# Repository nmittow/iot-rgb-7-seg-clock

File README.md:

# iot-rgb-7-seg-clock

RGB leds arranged to simulate the look of a 7 segment display.

Raspberry Pi &amp; ESP32 based controllers.

ESP32 version features: realtime clock, syncs to a network time server,  supports various time display animations.

All PCBs in KiCAD.

Raspberry Pi version features: all ESP32 features plus: 3.5mm audio jack and 5V relay controlled power output (for alarm audio), python library for controlling display &amp; alarm functionality (in-progress).

Motivation: I wanted an alarm that syncs with my various calendars (google, protonmail, etc) capable of 'smart' functionality like adjusting alarm time based on calendar events &amp; traffic conditions, etc., but wanted those calculations to happen locally (i.e. not google now/similar).  Love the look of 7 segment displays but wanted a bit more control of the display.

Construction: PCBs for controllers (ESP32 based &amp; Raspberry Pi cape), 7 segment digits are custom PCBs with APA102 addressable LEDs (3 per segment), daisy-chain-able.  3D Printed shrouds &amp; laser cut acrylic diffuser front, all in a stylish wooden box.  PCBs designed in KiCAD, 3D Modeling in AutoCAD & Fusion360.

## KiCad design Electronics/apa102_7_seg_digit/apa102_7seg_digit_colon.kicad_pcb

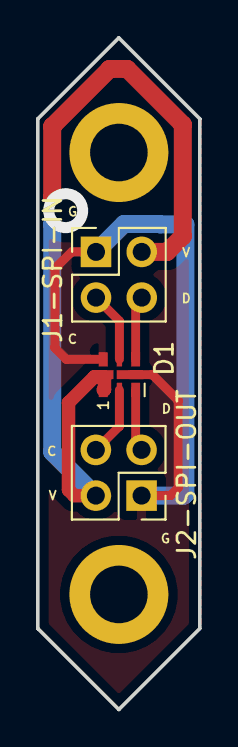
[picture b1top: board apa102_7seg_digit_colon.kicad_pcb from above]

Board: 2 copper layers, 9.0 x 37.3 mm, 3 parts (0 on the bottom side), 6 nets.

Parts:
D1: A_0; LED-APA102-2020
J1-SPI-IN: SPI_IN; PinHeader_2x02_P2.54mm_Vertical
J2-SPI-OUT: SPI_OUT; PinHeader_2x02_P2.54mm_Vertical

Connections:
+5V: D1.1, J1-SPI-IN.2, J2-SPI-OUT.2
GND: D1.6, J1-SPI-IN.1, J2-SPI-OUT.1
unnamed: D1.2, J2-SPI-OUT.4
unnamed: D1.3, J2-SPI-OUT.3
unnamed: D1.4, J1-SPI-IN.4
unnamed: D1.5, J1-SPI-IN.3

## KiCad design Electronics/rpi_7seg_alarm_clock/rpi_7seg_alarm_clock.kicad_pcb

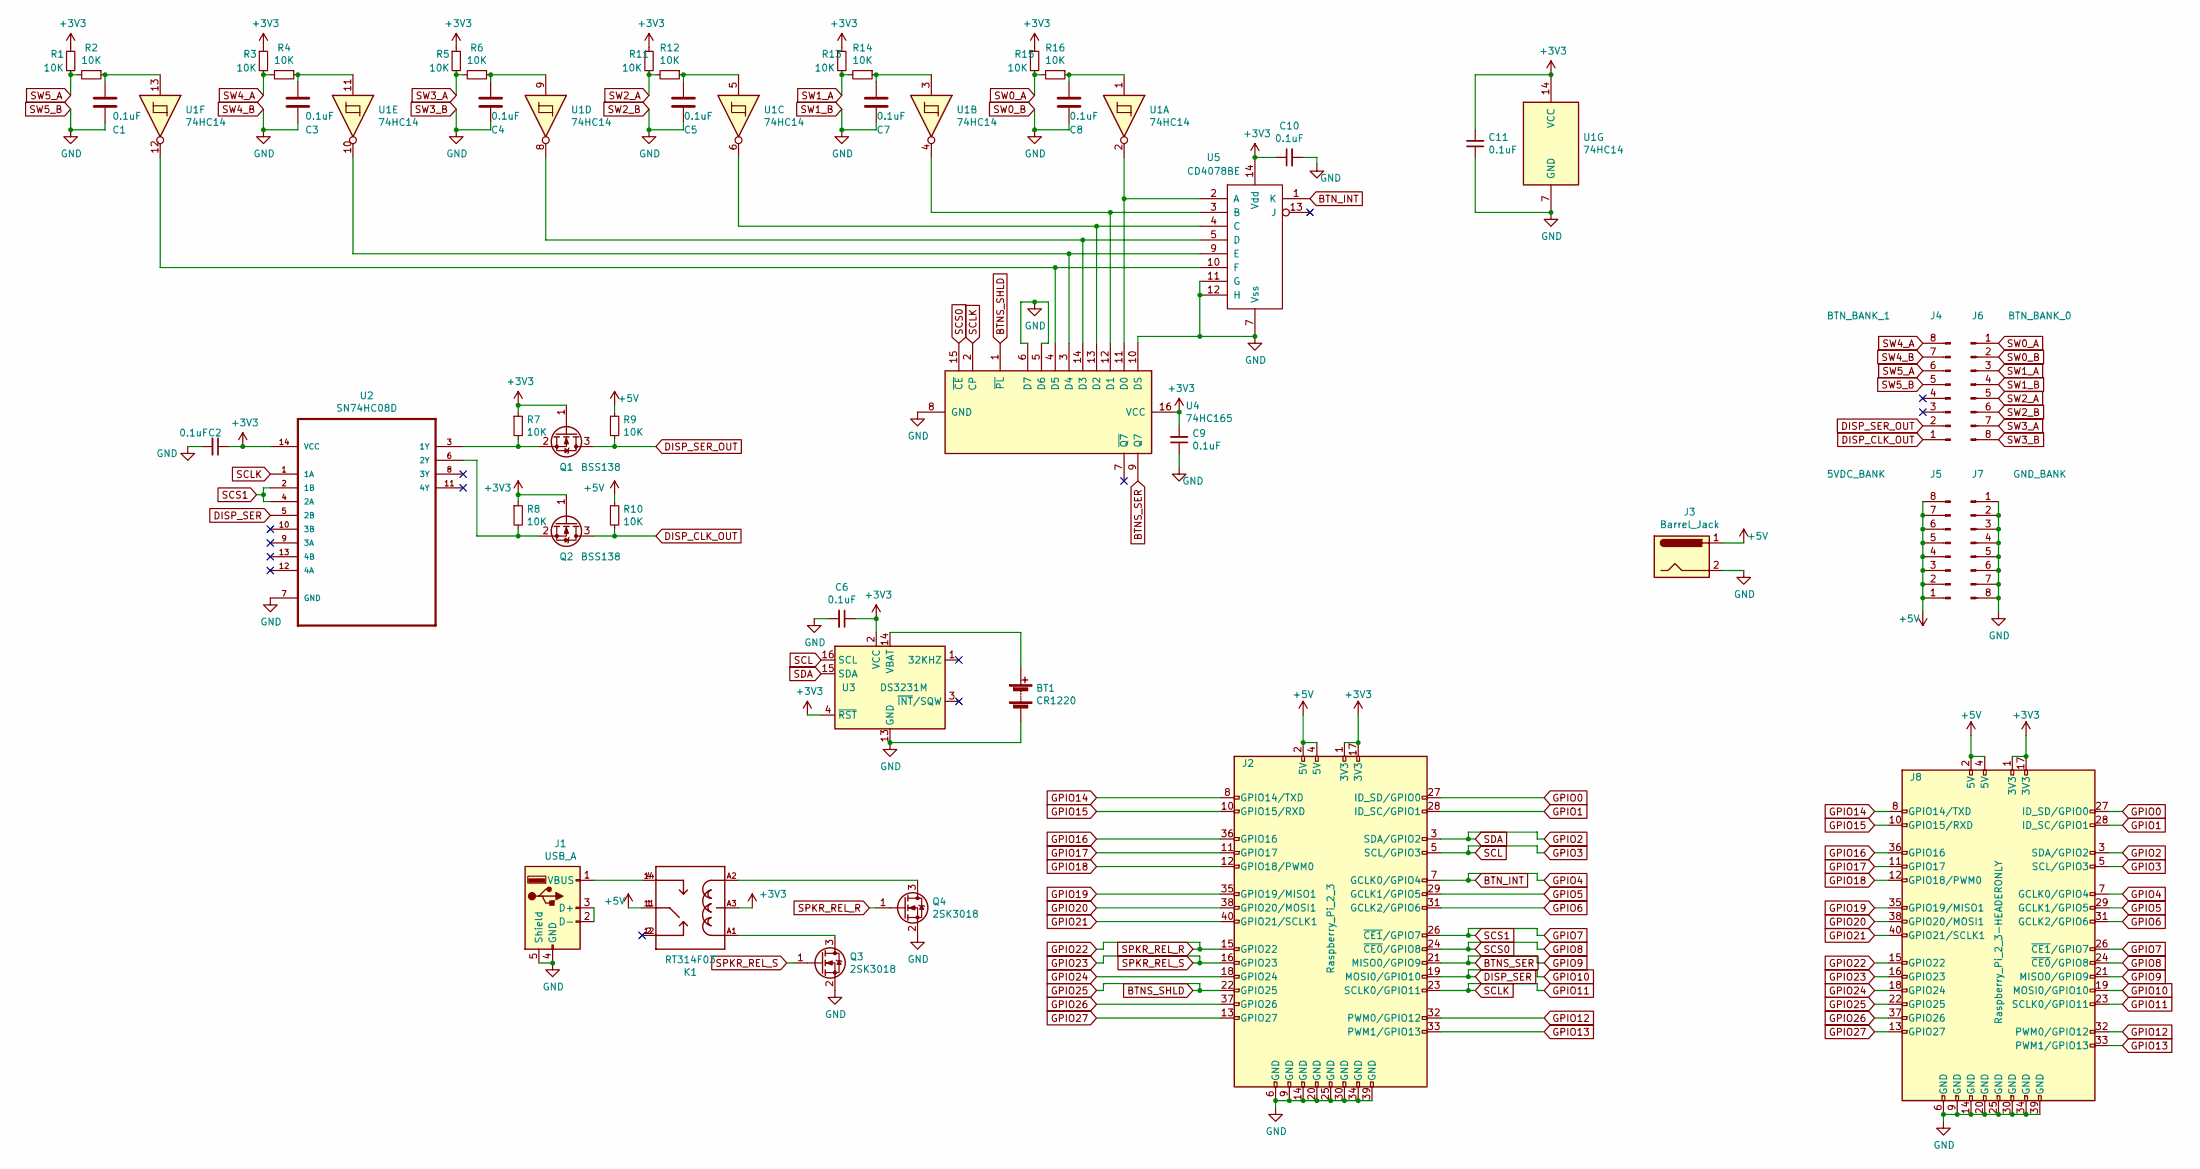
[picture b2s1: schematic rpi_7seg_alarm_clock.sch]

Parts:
BT1: CR1220; BatteryHolder_Keystone_3001_1x12mm
C1, C2, C3, C4, C5, C6, C7, C8, C9, C10, C11: 0.1uF; C_0805_2012Metric
J1: USB_A; USB_A_Molex_67643_Horizontal
J2: Raspberry_Pi_2_3; PinHeader_2x20_P2.54mm_Vertical
J3: Barrel_Jack; PinHeader_1x02_P2.54mm_Vertical
J4: BTN_BANK_1; TerminalBlock_Phoenix_PT-1,5-8-3.5-H_1x08_P3.50mm_Horizontal
J5: 5VDC_BANK; TerminalBlock_Phoenix_PT-1,5-8-3.5-H_1x08_P3.50mm_Horizontal
J6: BTN_BANK_0; TerminalBlock_Phoenix_PT-1,5-8-3.5-H_1x08_P3.50mm_Horizontal
J7: GND_BANK; TerminalBlock_Phoenix_PT-1,5-8-3.5-H_1x08_P3.50mm_Horizontal
J8: Raspberry_Pi_2_3-HEADERONLY; PinHeader_2x20_P2.54mm_Vertical
K1: RT314F03; RELAY_RT314F03
Q1, Q2: BSS138; SOT-23
Q3, Q4: 2SK3018; SOT-323_SC-70
R1, R2, R3, R4, R5, R6, R7, R8, R9, R10, R11, R12, R13, R14, R15, R16: 10K; R_0805_2012Metric
U1: 74HC14; SOIC-14_3.9x8.7mm_P1.27mm
U2: SN74HC08D; SOIC127P600X175-14N
U3: DS3231M; SOIC-16W_7.5x10.3mm_P1.27mm
U4: 74HC165; TSSOP-16_4.4x5mm_P0.65mm
U5: CD4078BE; TSSOP-14_4.4x5mm_P0.65mm

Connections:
+3V3: C2.1, C6.1, C9.2, C10.1, C11.2, J2.1 (3V3), J2.17 (3V3), J8.1 (3V3), J8.17 (3V3), K1.A3, Q1.1 (G), Q2.1 (G), R1.1, R3.1, R5.1, R7.1, R8.1, R11.1, R13.1, R15.1, U1.14 (VCC), U2.14 (VCC), U3.2 (VCC), U3.4 (~RST), U4.16 (VCC), U5.14 (Vdd)
+5V: J2.2 (5V), J2.4 (5V), J3.1, J5.1, J5.2, J5.3, J5.4, J5.5, J5.6, J5.7, J5.8, J8.2 (5V), J8.4 (5V), K1.1, K1.11, R9.1, R10.1
BTNS_SER: J2.21 (MISO0/GPIO9), J8.21 (MISO0/GPIO9), U4.9 (Q7)
BTNS_SHLD: J2.22 (GPIO25), J8.22 (GPIO25), U4.1 (~PL)
BTN_INT: J2.7 (GCLK0/GPIO4), J8.7 (GCLK0/GPIO4), U5.1 (K)
DISP_CLK_OUT: J4.1, Q2.3 (D), R10.2
DISP_SER: J2.19 (MOSI0/GPIO10), J8.19 (MOSI0/GPIO10), U2.5 (2B)
DISP_SER_OUT: J4.2, Q1.3 (D), R9.2
GPIO0: J2.27 (ID_SD/GPIO0), J8.27 (ID_SD/GPIO0)
GPIO1: J2.28 (ID_SC/GPIO1), J8.28 (ID_SC/GPIO1)
GPIO2: J2.3 (SDA/GPIO2), J8.3 (SDA/GPIO2), U3.15 (SDA)
GPIO3: J2.5 (SCL/GPIO3), J8.5 (SCL/GPIO3), U3.16 (SCL)
GPIO5: J2.29 (GCLK1/GPIO5), J8.29 (GCLK1/GPIO5)
GPIO6: J2.31 (GCLK2/GPIO6), J8.31 (GCLK2/GPIO6)
GPIO7: J2.26 (~CE1~/GPIO7), J8.26 (~CE1~/GPIO7), U2.2 (1B), U2.4 (2A)
GPIO8: J2.24 (~CE0~/GPIO8), J8.24 (~CE0~/GPIO8), U4.15 (~CE)
GPIO11: J2.23 (SCLK0/GPIO11), J8.23 (SCLK0/GPIO11), U2.1 (1A), U4.2 (CP)
GPIO12: J2.32 (PWM0/GPIO12), J8.32 (PWM0/GPIO12)
GPIO13: J2.33 (PWM1/GPIO13), J8.33 (PWM1/GPIO13)
GPIO14: J2.8 (GPIO14/TXD), J8.8 (GPIO14/TXD)
GPIO15: J2.10 (GPIO15/RXD), J8.10 (GPIO15/RXD)
GPIO16: J2.36 (GPIO16), J8.36 (GPIO16)
GPIO17: J2.11 (GPIO17), J8.11 (GPIO17)
GPIO18: J2.12 (GPIO18/PWM0), J8.12 (GPIO18/PWM0)
GPIO19: J2.35 (GPIO19/MISO1), J8.35 (GPIO19/MISO1)
GPIO20: J2.38 (GPIO20/MOSI1), J8.38 (GPIO20/MOSI1)
GPIO21: J2.40 (GPIO21/SCLK1), J8.40 (GPIO21/SCLK1)
GPIO22: J2.15 (GPIO22), J8.15 (GPIO22), Q4.1 (G)
GPIO23: J2.16 (GPIO23), J8.16 (GPIO23), Q3.1 (G)
GPIO24: J2.18 (GPIO24), J8.18 (GPIO24)
GPIO26: J2.37 (GPIO26), J8.37 (GPIO26)
GPIO27: J2.13 (GPIO27), J8.13 (GPIO27)
unnamed: BT1.1 (+), U3.14 (VBAT)
unnamed: C1.1, R2.1, U1.13
unnamed: C3.1, R4.1, U1.11
unnamed: C4.1, R6.1, U1.9
unnamed: C5.1, R12.1, U1.5
unnamed: C7.1, R14.1, U1.3
unnamed: C8.1, R16.1, U1.1
unnamed: J1.1 (VBUS), K1.4, K1.14
unnamed: J1.2 (D-), J1.3 (D+)
unnamed: K1.2, K1.12
unnamed: K1.A1, Q3.3 (D)
unnamed: K1.A2, Q4.3 (D)
unnamed: Q1.2 (S), R7.2, U2.3 (1Y)
unnamed: Q2.2 (S), R8.2, U2.6 (2Y)
unnamed: U1.2, U4.11 (D0), U5.2 (A)
unnamed: U1.4, U4.12 (D1), U5.3 (B)
unnamed: U1.6, U4.13 (D2), U5.4 (C)
unnamed: U1.8, U4.14 (D3), U5.5 (D)
unnamed: U1.10, U4.3 (D4), U5.9 (E)
unnamed: U1.12, U4.4 (D5), U5.10 (F)
SW0_A: J6.1, R15.2, R16.2
SW0_B: BT1.2 (-), C1.2, C2.2, C3.2, C4.2, C5.2, C6.2, C7.2, C8.2, C9.1, C10.2, C11.1, J1.4 (GND), J1.5 (Shield), J2.6 (GND), J2.9 (GND), J2.14 (GND), J2.20 (GND), J2.25 (GND), J2.30 (GND), J2.34 (GND), J2.39 (GND), J3.2, J4.5, J4.7, J6.2, J6.4, J6.6, J6.8, J7.1, J7.2, J7.3, J7.4, J7.5, J7.6, J7.7, J7.8, J8.6 (GND), J8.9 (GND), J8.14 (GND), J8.20 (GND), J8.25 (GND), J8.30 (GND), J8.34 (GND), J8.39 (GND), Q3.2 (S), Q4.2 (S), U1.7 (GND), U2.7 (GND), U3.5 (GND), U3.6 (GND), U3.7 (GND), U3.8 (GND), U3.9 (GND), U3.10 (GND), U3.11 (GND), U3.12 (GND), U3.13 (GND), U4.5 (D6), U4.6 (D7), U4.8 (GND), U4.10 (DS), U5.7 (Vss), U5.11 (G), U5.12 (H)
SW1_A: J6.3, R13.2, R14.2
SW2_A: J6.5, R11.2, R12.2
SW3_A: J6.7, R5.2, R6.2
SW4_A: J4.8, R3.2, R4.2
SW5_A: J4.6, R1.2, R2.2

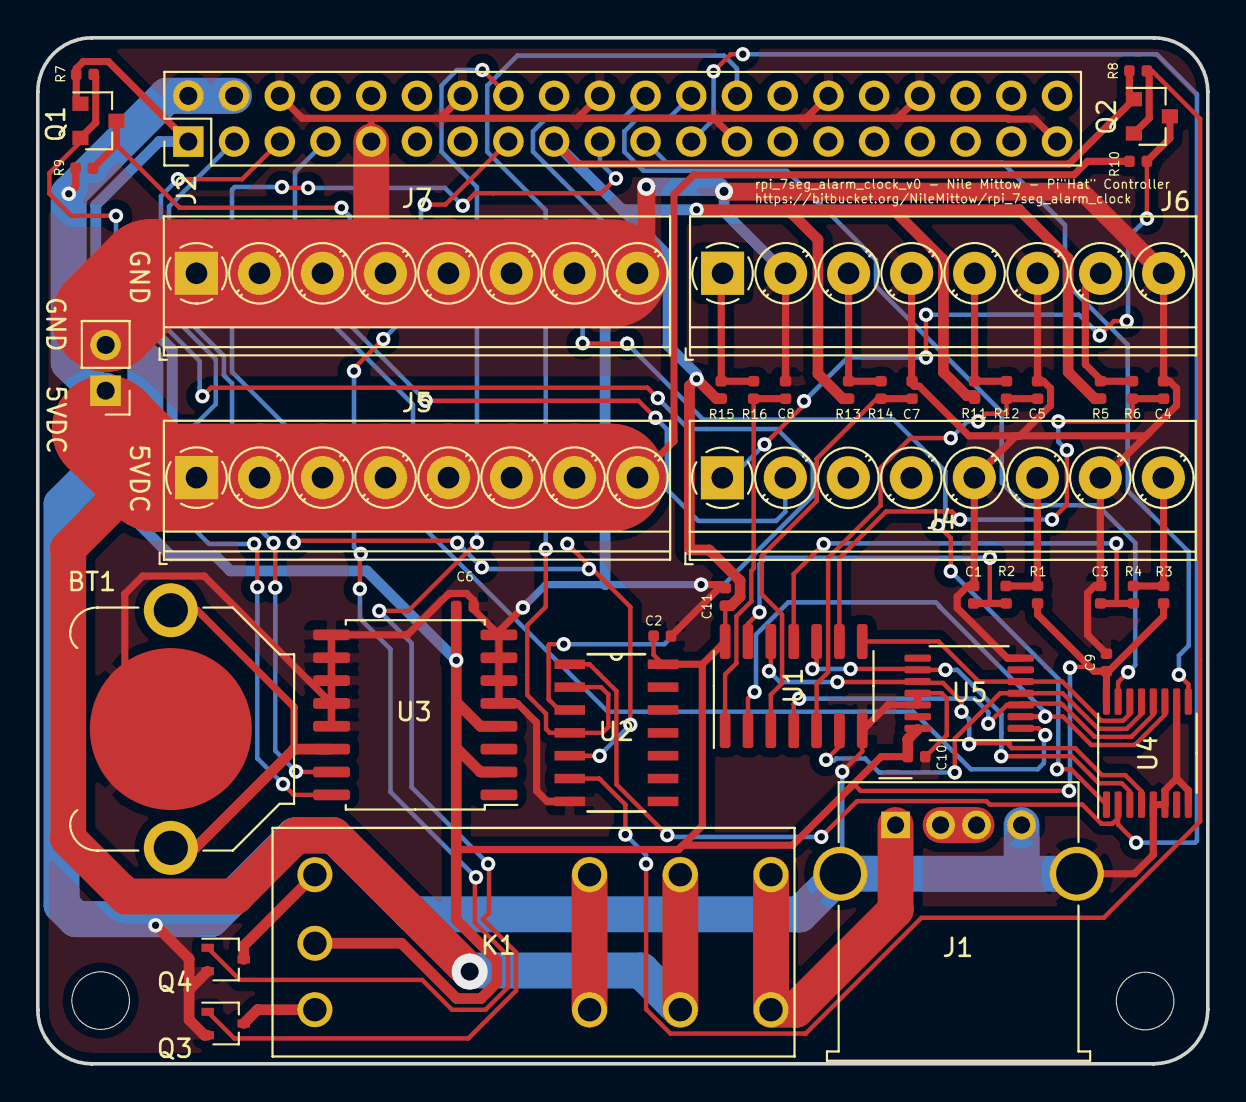
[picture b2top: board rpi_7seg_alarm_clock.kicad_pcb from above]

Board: 2 copper layers, 65.0 x 57.0 mm, 46 parts (1 on the bottom side), 42 nets.

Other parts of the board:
nilesface: nilesface_small

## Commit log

2022-07-25 initial upload of all designs thus far
2022-07-25 added images
